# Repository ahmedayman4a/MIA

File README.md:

# Latest Changes

Add motor RPM controller

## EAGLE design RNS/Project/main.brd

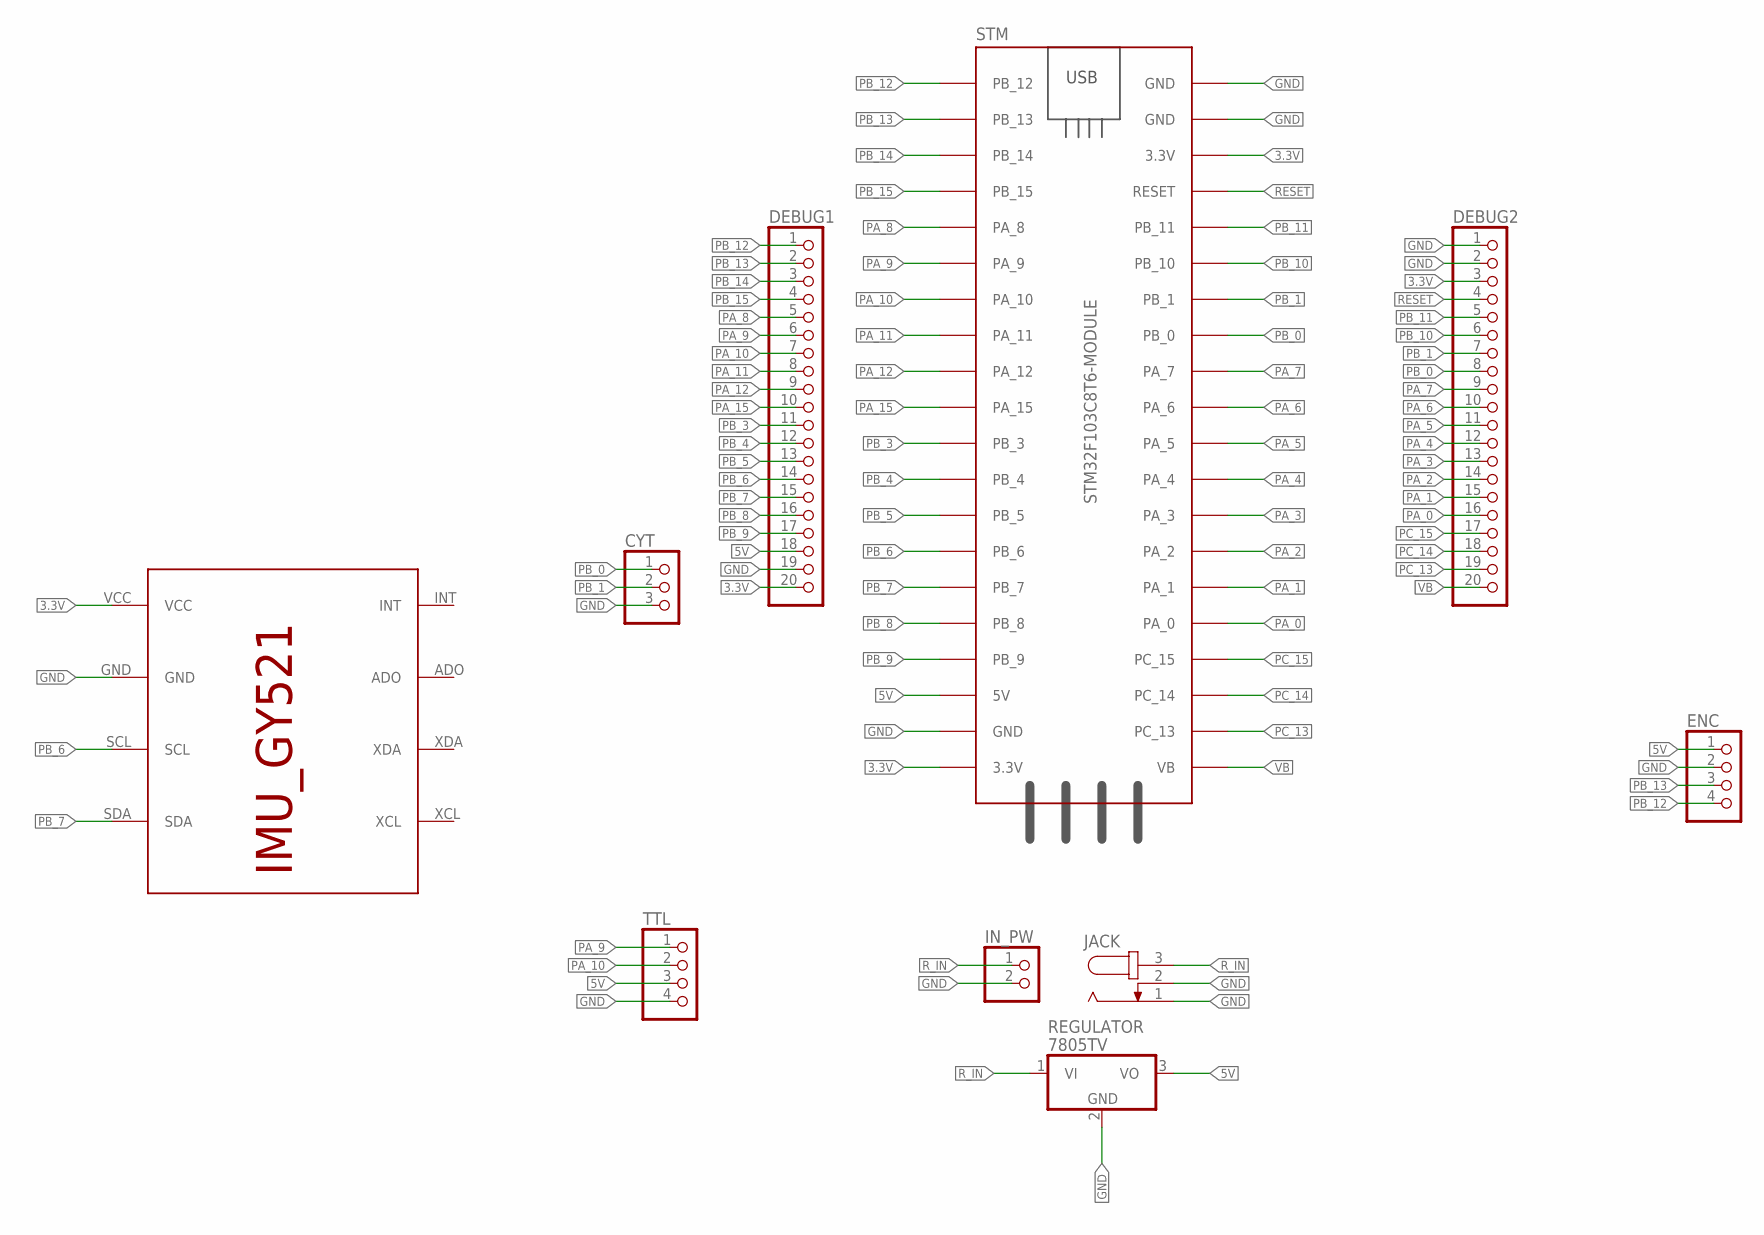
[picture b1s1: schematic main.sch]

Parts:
CYT: PINHD-1X3; 1X03
DEBUG1, DEBUG2: PINHD-1X20; 1X20
ENC: PINHD-1X4; 1X04
IMU: IMU_ROBOCON_GY521; IMU_GY521
IN_PW: PINHD-2_DATA; 1X02_DATA
JACK: JACK-PLUG0; SPC4077
REGULATOR: 7805TV; TO220V
STM: STM32F103C8T6-MODULE
TTL: PINHD-1X4; 1X04

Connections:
3.3V: DEBUG1.20, DEBUG2.3, IMU.VCC, STM.3.3V_1 (3.3V), STM.3.3V_2 (3.3V)
5V: DEBUG1.18, ENC.1, REGULATOR.3 (VO), STM.5V, TTL.3
GND: CYT.3, DEBUG1.19, DEBUG2.1, DEBUG2.2, ENC.2, IMU.GND, IN_PW.2, JACK.1, JACK.2, REGULATOR.2 (GND), STM.GND_1 (GND), STM.GND_2 (GND), STM.GND_3 (GND), TTL.4
PA_0: DEBUG2.16, STM.PA_0
PA_1: DEBUG2.15, STM.PA_1
PA_2: DEBUG2.14, STM.PA_2
PA_3: DEBUG2.13, STM.PA_3
PA_4: DEBUG2.12, STM.PA_4
PA_5: DEBUG2.11, STM.PA_5
PA_6: DEBUG2.10, STM.PA_6
PA_7: DEBUG2.9, STM.PA_7
PA_8: DEBUG1.5, STM.PA_8
PA_9: DEBUG1.6, STM.PA_9, TTL.1
PA_10: DEBUG1.7, STM.PA_10, TTL.2
PA_11: DEBUG1.8, STM.PA_11
PA_12: DEBUG1.9, STM.PA_12
PA_15: DEBUG1.10, STM.PA_15
PB_0: CYT.1, DEBUG2.8, STM.PB_0
PB_1: CYT.2, DEBUG2.7, STM.PB_1
PB_3: DEBUG1.11, STM.PB_3
PB_4: DEBUG1.12, STM.PB_4
PB_5: DEBUG1.13, STM.PB_5
PB_6: DEBUG1.14, IMU.SCL, STM.PB_6
PB_7: DEBUG1.15, IMU.SDA, STM.PB_7
PB_8: DEBUG1.16, STM.PB_8
PB_9: DEBUG1.17, STM.PB_9
PB_10: DEBUG2.6, STM.PB_10
PB_11: DEBUG2.5, STM.PB_11
PB_12: DEBUG1.1, ENC.4, STM.PB_12
PB_13: DEBUG1.2, ENC.3, STM.PB_13
PB_14: DEBUG1.3, STM.PB_14
PB_15: DEBUG1.4, STM.PB_15
PC_13: DEBUG2.19, STM.PC_13
PC_14: DEBUG2.18, STM.PC_14
PC_15: DEBUG2.17, STM.PC_15
RESET: DEBUG2.4, STM.RESET
R_IN: IN_PW.1, JACK.3, REGULATOR.1 (VI)
VB: DEBUG2.20, STM.VB

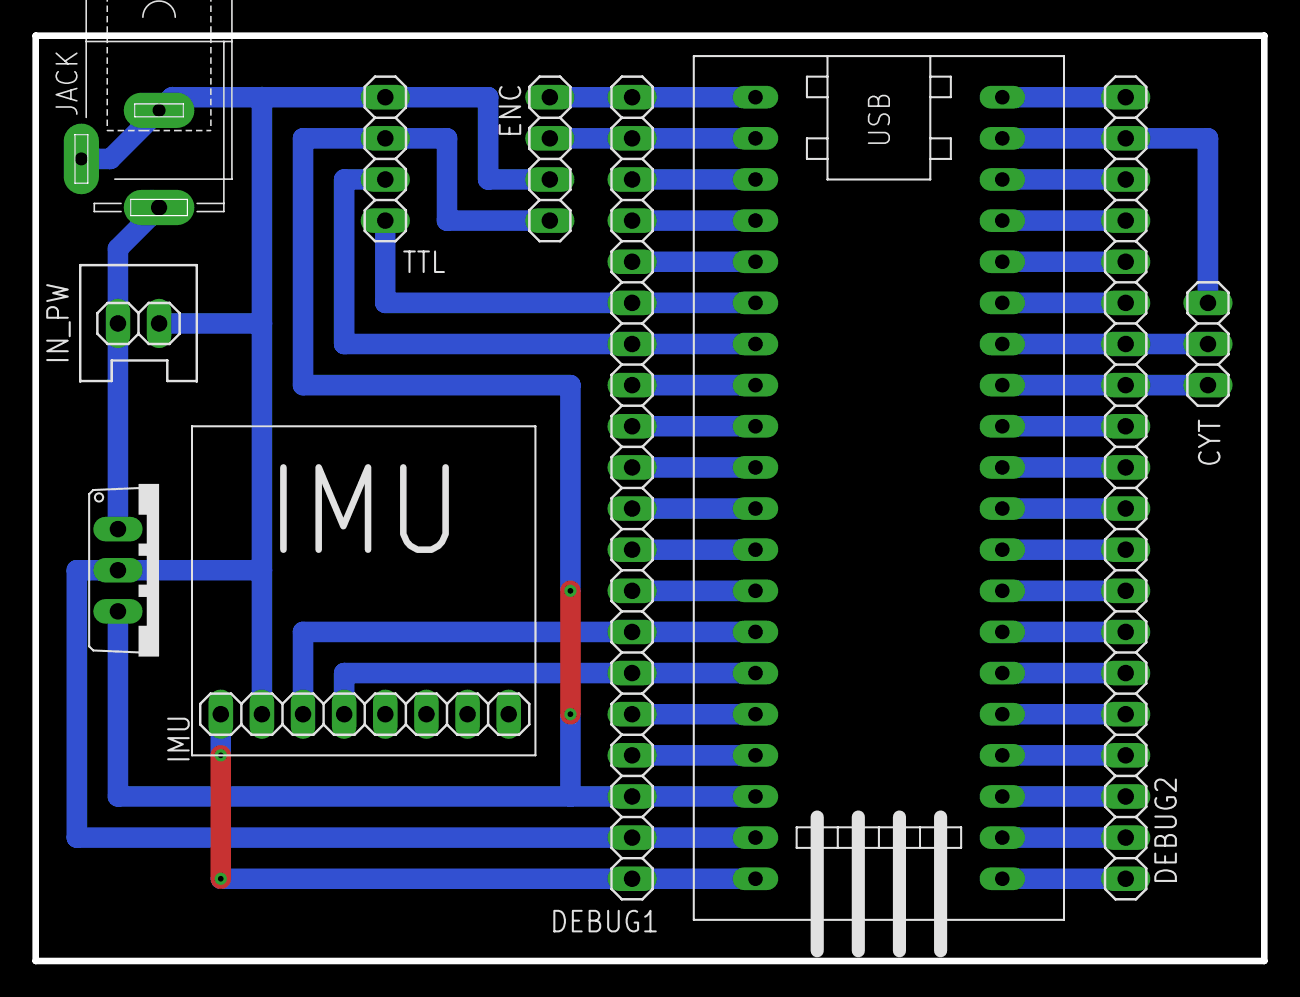
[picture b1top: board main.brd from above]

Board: 2 copper layers, 75.9 x 57.1 mm, 10 parts (0 on the bottom side), 38 nets.

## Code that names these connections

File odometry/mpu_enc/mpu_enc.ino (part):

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// ===                      Pins Definitions                    ===
// ================================================================

#define PIN_SDA PB_7
#define PIN_SCL PB_6

#define PIN_RX PA_10
#define PIN_TX PA_9

#define PIN_ENC_X_A PB_12
#define PIN_ENC_X_B PB_13

#define PIN_ENC_Y_A PB_12
#define PIN_ENC_Y_B PB_13

// ================================================================
// ===                  Robot Specs Definitions                 ===
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
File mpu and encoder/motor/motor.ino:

#include <ros.h>
#include <std_msgs/Int64.h>
#include <std_msgs/Int32.h>
#include <std_msgs/String.h>
#include "time_helper.h"
#include "encoder.h"
#include "motor_pid.h"

#define encoderA_pin PA_15
#define encoderB_pin PB_3

#define motor_pwm_pin PA_6
#define motor_dir_pin PA_7
#define max_rpm 500
#define set_point 150

ros::NodeHandle nh;

std_msgs::Int64 encoder_msg;
std_msgs::String output_msg;
ros::Publisher encoder("encoder", &encoder_msg);
ros::Publisher output("Output", &output_msg);

long encoderCount = 0;

// void rpm_recieved(const std_msgs::Int32 &rpm_msg) {
//   int rpm = rpm_msg.data;
//   set_motor_speed(rpm);
// }

//ros::Subscriber<std_msgs::Int32> sub("controlled_rpm", &rpm_recieved);
TimeHelper t = TimeHelper();
void setup() {
  // initialize serial communication
  Serial.setRx(PB_11);
  Serial.setTx(PB_10);
  Serial.begin(115200);

  // intialize node
  (nh.getHardware())->setPort(&Serial);
  (nh.getHardware())->setBaud(115200);
  nh.initNode();
  nh.advertise(encoder);
  nh.advertise(output);

  pinMode(encoderA_pin, INPUT_PULLUP);
  pinMode(encoderA_pin, INPUT_PULLUP);
  pinMode(motor_pwm_pin, OUTPUT);
  pinMode(motor_dir_pin, OUTPUT);

  attachInterrupt(digitalPinToInterrupt(encoderA_pin), IRQ_encoder_A, CHANGE);
  attachInterrupt(digitalPinToInterrupt(encoderB_pin), IRQ_encoder_B, CHANGE);
}

void loop() {
  encoder_msg.data = encoderCount;
  encoder.publish(&encoder_msg);
  delay(5);

  double dt = t.get_dt();

  Encoder encoderManager = Encoder(540.0);

  double rpm = encoderManager.count_to_rpm(encoderCount, dt, nh);
  String output_str;
  output_str = "dt : ";
  output_str += String(dt, 5);
  //if (dt > 0) {
  MotorPID motor_pid = MotorPID(set_point, 50, 0, 0);
  double controlled_rpm = motor_pid.get_controlled_rpm(rpm, dt);
  set_motor_speed((int)controlled_rpm);
  double error = set_point - rpm;

  output_str += ";;;;Encoder count : ";
  output_str += String(encoderCount);
  output_str += ";;;;Controlled : ";
  output_str += String(controlled_rpm);
  output_str += ";;;;Actual rpm : ";
  output_str += String(rpm, 5);
  output_str += ";;;;Set point : ";
  output_str += String(set_point);
  output_str += ";;;;Error : ";
  output_str += String(error);
  //}
  output_msg.data = output_str.c_str();
  output.publish(&output_msg);


  nh.spinOnce();
}

void IRQ_encoder_A() {
  encoderCount += (digitalRead(encoderA_pin) == digitalRead(encoderB_pin)) ? 1 : -1;
}

void IRQ_encoder_B() {
  encoderCount += (digitalRead(encoderA_pin) == digitalRead(encoderB_pin)) ? -1 : 1;
}

void set_motor_speed(int rpm) {
  bool opposite_dir = rpm < 0;
  rpm = abs(rpm);
  int dutyCycle = map(rpm, 0, max_rpm, 0, 65535);
  analogWrite(motor_pwm_pin, dutyCycle);
  analogWrite(motor_dir_pin, opposite_dir);
}

void set_motor_speed(int dutyCycle) {
  bool opposite_dir = dutyCycle < 0;
  dutyCycle = abs(dutyCycle);
  //int dutyCycle = map(rpm, 0, max_rpm, 0, 65535);
  dutyCycle = constrain(dutyCycle,0,65535);
  analogWrite(motor_pwm_pin, dutyCycle);
  analogWrite(motor_dir_pin, opposite_dir);
}

float low_pass(float v_new, float v_filtered_old, float dt, int cutoff = 25) {
  float alpha = dt / (dt + 1 / (2 * PI * cutoff));
  float v_filtered_new = v_new * alpha + (1 - alpha) * v_filtered_old;
  return v_filtered_new;
}

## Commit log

2022-10-10 Add RNS files
2022-10-11 Change design to fit IMU and Power Base inside the board
2022-10-11 Add pdf board designs
2022-10-11 Add photoshop design files for board papers
2022-10-16 Add mpu and encoder tasks
2022-10-17 Fix Int64 library not found and some variable names
2022-10-18 Add ros package for RNS and kalman filter
2022-10-22 Add launch file
2022-10-22 Update README to show change: adding launch file
2022-10-24 Remove unneeded library
2022-10-24 Add motor rpm controller
2022-10-24 Update README to reflect motor control code
2022-10-30 Add classic opencv task
2022-11-04 Added yolov4 model and results
2022-11-10 Code changes at war4a
2022-11-10 Add odometry localization
